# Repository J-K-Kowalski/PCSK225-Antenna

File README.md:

# PCSK225-Antenna

<ul>
<li>2026-08-02 - recalculate resistors value</li>
<li>2024-10-08 - fixed GND symbol</li>
<li>2024-06-18 - new version of Ferrite Holder</li>
</ul>

<p>This simple active antenna is designed to receive the time signal from the PCSK-225 transmitter in Solec Kujawski, Poland.

<p>It allows you to reliably receive UTC(pl) time frames transmitted by the <a href="https://e-czas.gum.gov.pl/e-czas-radio/" target=_blank>Central Office of Measures</a> using this transmitter. Receiver documentation is available at https://github.com/e-czasPL/TimeReceiver225kHz.

The project uses a ferrite antenna from a cheap and popular DCF receiver available, for example, on Aliexpress. Such an antenna has an inductance of approximately 1.5mH. You need to use 333pF capacitors (270pF + 56pF + trimmer 6-25pF) which will allow you to tune the resonant circuit to 225kHz.

The transistor BF545, MMBFJ108 (SMD) or BF245/J211 (THT) was used as an amplifier - only one should be installed.

If a long-wave ferrite antenna (from an old radio) with an inductance of about 4-6mH is used, the capacitors should be reduced to about 100pF.

<ul>
<li>In the /KiCAD folder, you will find a project in the KiCAD 10.0 format;
<li>In the /3D folder, you will find models of the holder and the entire antenna in STEP, STL formats;
</ul>

<p>The long wave signal of the First Polish Radio Program reaches a large part of Europe. You can see the coverage map below.

<p>
<table border=0 cellpadding=0 cellspacing=0 width=100%>
<tr><td>
</td><td></td></tr>
</table>

<ul>
<li>2024-06-18 - Nowa wersja modelu 3D do wydruku uchwytu na pręt ferrytowy</li>
</ul>

<p>Ta prosta aktywna antena jest zaprojektowana do odbioru sygnału czasu z nadajnika PCSK-225 w Solec Kujawski, Polska.

<p>Pozwala ona niezawodnie odbierać ramki czasu UTC(pl) nadawane przez <a href="https://e-czas.gum.gov.pl/e-czas-radio/" target=_blank>Główny Urząd Miar</a> za pomocą tego nadajnika. Dokumentacja odbiornika jest dostępna na https://github.com/e-CzasPL/TimeReceiver225kHz.

W projekcie użyto anteny ferrytowej od taniego i popularnego odbiornika DCF dostępnego np. na Aliexpress. Taka antena ma indukcyjność ok 1.5mH. Dlatego trzeba użyć kondensatorów 333pF (270pF + 56pF + trymer 6-25pF) co pozwoli zestroić obwód rezonansowy na 225 kHz.

Jako wzmacniacz użyto tranzystora BF545 lub MMBFJ108 (SMD) lub BF245/J211 (THT) - należy zamontować tylko jeden z nich.

Jeżeli zostanie użyta antena ferrytowa na fale długie (ze starego radia) o indukcyjności ok. 4-6mH to należy kondensatory zmniejszyć do ok 100pF.

<ul>
<li>W folderze /KiCAD znajdziesz projekt w formacie KiCAD 10;
<li>W folderze /3D znajdziesz modele uchwytu i całej anteny w formatach STEP, STL;
</ul>

<p>Sygnał fal długich Programu Pierwszego Polskiego Radia dociera do dużej części Europy. Powyżej możesz zobaczyć mapę zasięgu.

<p>Jerzy K. Kowalski<br>Marek Mańkowski

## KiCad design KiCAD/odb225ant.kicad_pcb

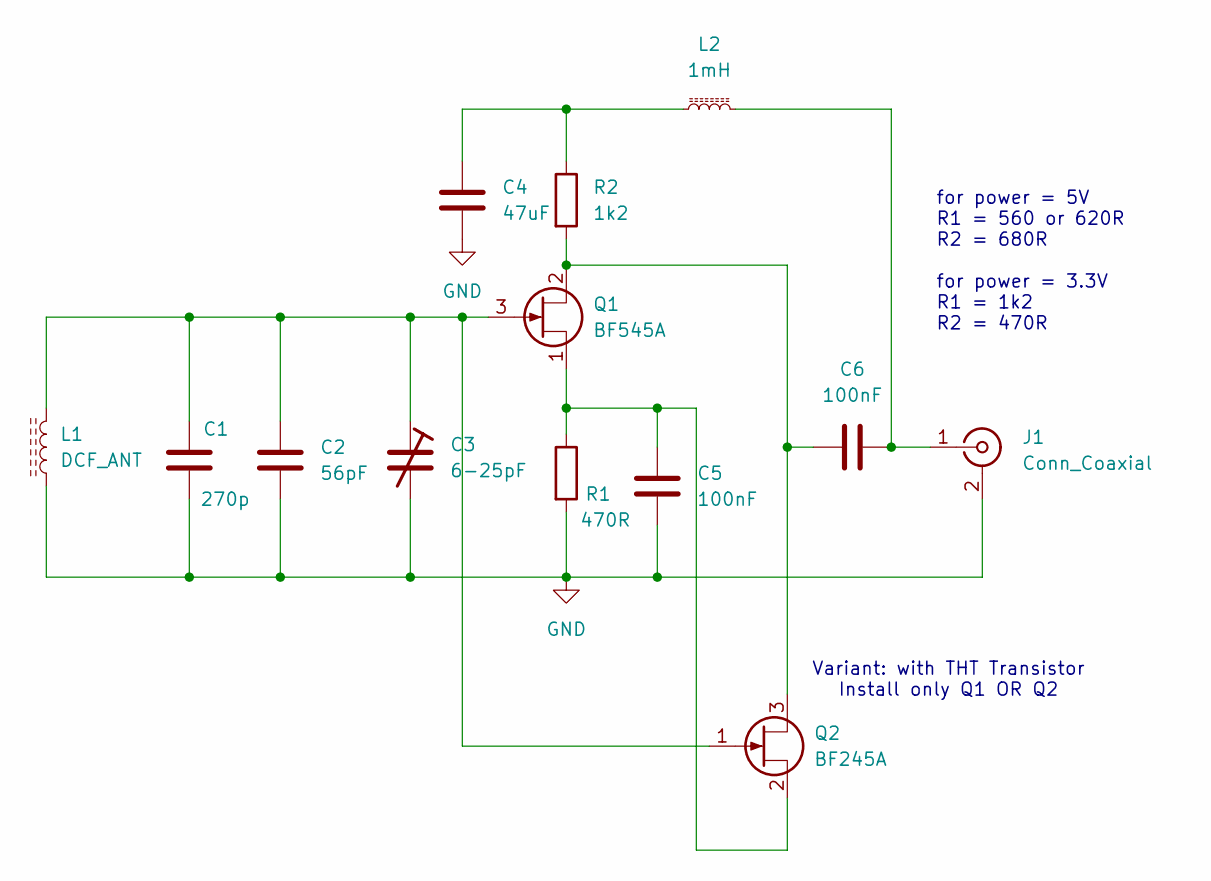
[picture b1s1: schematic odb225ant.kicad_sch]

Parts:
C1: 270p; C_0603_1608Metric_Pad1.08x0.95mm_HandSolder
C2: 56pF; C_0603_1608Metric_Pad1.08x0.95mm_HandSolder
C3: 6-25pF; C_Trimmer_Murata_TZB4-B
C4: 47uF; C_0603_1608Metric_Pad1.08x0.95mm_HandSolder
C5, C6: 100nF; C_0603_1608Metric_Pad1.08x0.95mm_HandSolder
J1: Conn_Coaxial; BNC_Horizontal
L1: DCF_ANT; PinHeader_1x02_P2.54mm_Vertical
L2: 1mH; L_Axial_L12.0mm_D5.0mm_P15.24mm_Horizontal_Fastron_MISC
Q1: BF545A; SOT-23
Q2: BF245A; TO-92_Inline
R1: 470R; R_0603_1608Metric_Pad0.98x0.95mm_HandSolder
R2: 1k2; R_0603_1608Metric_Pad0.98x0.95mm_HandSolder

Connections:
GND: C1.2, C2.2, C3.2, C4.2, C5.2, J1.2 (Ext), L1.2, R1.2
unnamed: C4.1, L2.1, R2.1
unnamed: C6.2, J1.1 (In), L2.2
unnamed: C6.1, Q1.2 (D), Q2.3 (D), R2.2
unnamed: C1.1, C2.1, C3.1, L1.1, Q1.3 (G), Q2.1 (G)
unnamed: C5.1, Q1.1 (S), Q2.2 (S), R1.1

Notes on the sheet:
Variant: with THT Transistor Install only Q1 OR Q2
for power = 5V R1 = 560 or 620R R2 = 680R for power = 3.3V R1 = 1k2 R2 = 470R

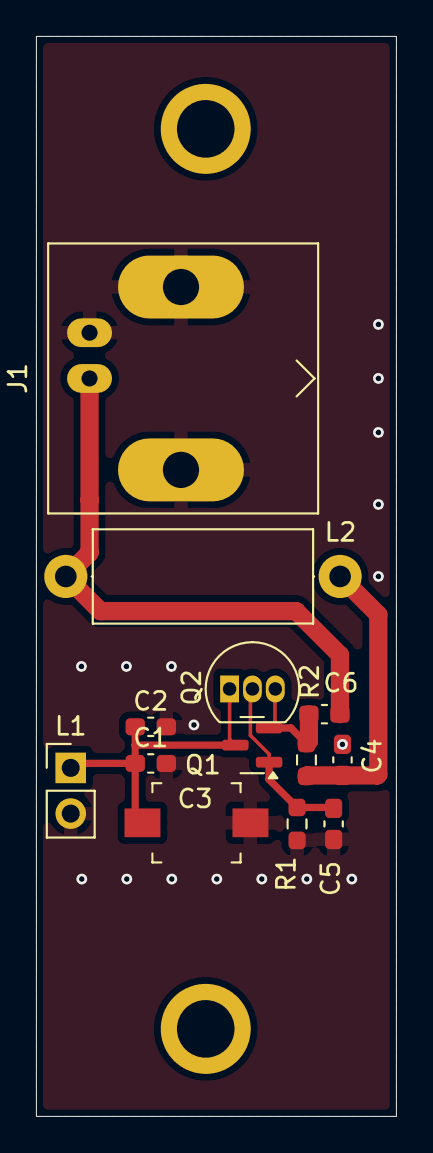
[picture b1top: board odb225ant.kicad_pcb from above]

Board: 2 copper layers, 20.0 x 60.0 mm, 13 parts (0 on the bottom side), 6 nets.

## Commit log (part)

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2024-04-10 first step
2024-04-10 add project and 3D models
2024-04-10 modify readme
2024-04-10 modify doc
2024-06-18 FerriteHolder new model 3D
2024-10-08 fixed C4 GND symbol

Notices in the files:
KiCAD/odb225ant.kicad_pcb:
© e4Science,
Marek Mankowski 2024
